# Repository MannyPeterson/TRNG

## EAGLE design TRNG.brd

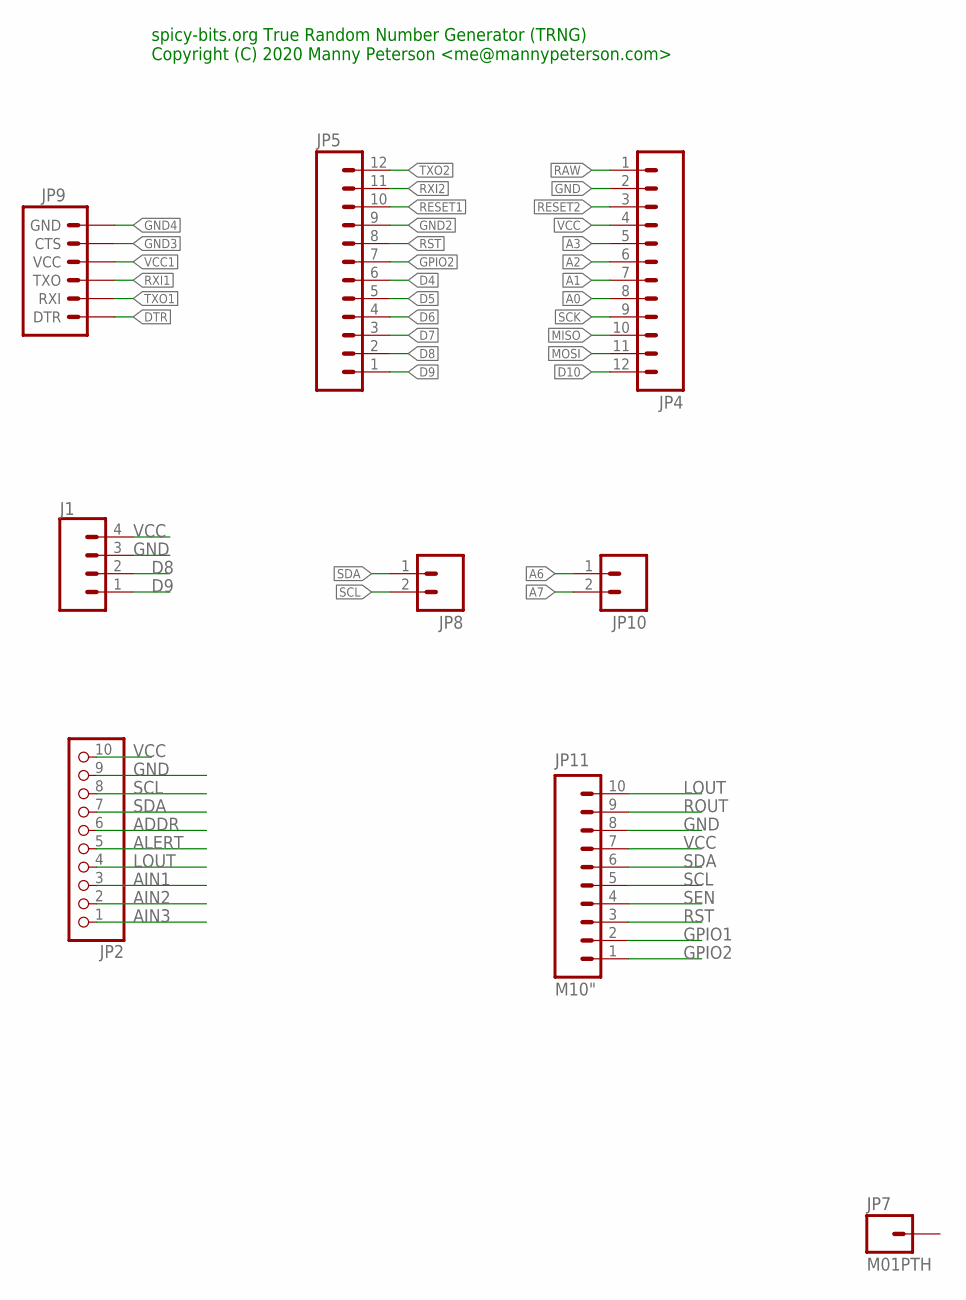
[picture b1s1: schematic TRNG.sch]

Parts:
J1: CONN_04PTH; 1X04
JP2: HEADER-1X1070MIL; 1X10_ROUND70
JP4, JP5: M12PTH; 1X12
JP7: M01PTH; 1X01
JP8, JP10: M02PTH; 1X02
JP9: ARDUINO_SERIAL_PROGRAMPTH; 1X06
JP11: M10"; 1X10

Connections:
A0: JP4.8
A1: JP4.7
A2: JP4.6
A3: JP4.5
A6: JP10.1
A7: JP10.2
ADDR: JP2.6
AIN1: JP2.3
AIN2: JP2.2
AIN3: JP2.1
ALERT: JP2.5
D4: JP5.6
D5: JP5.5
D6: JP5.4
D7: JP5.3
D8: J1.2, JP5.2
D9: J1.1, JP5.1
D10: JP4.12
DTR: JP9.1 (DTR)
GND: J1.3, JP2.9, JP4.2, JP11.8
GND2: JP5.9
GND3: JP9.5 (CTS)
GND4: JP9.6 (GND)
GPIO1: JP11.2
GPIO2: JP5.7, JP11.1
LOUT: JP2.4, JP11.10
MISO: JP4.10
MOSI: JP4.11
RAW: JP4.1
RESET1: JP5.10
RESET2: JP4.3
ROUT: JP11.9
RST: JP5.8, JP11.3
RXI1: JP9.3 (TXO)
RXI2: JP5.11
SCK: JP4.9
SCL: JP2.8, JP8.2, JP11.5
SDA: JP2.7, JP8.1, JP11.6
SEN: JP11.4
TXO1: JP9.2 (RXI)
TXO2: JP5.12
VCC: J1.4, JP2.10, JP4.4, JP11.7
VCC1: JP9.4 (VCC)

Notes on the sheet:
spicy-bits.org True Random Number Generator (TRNG) Copyright (C) 2020 Manny Peterson <me@mannypeterson.com>

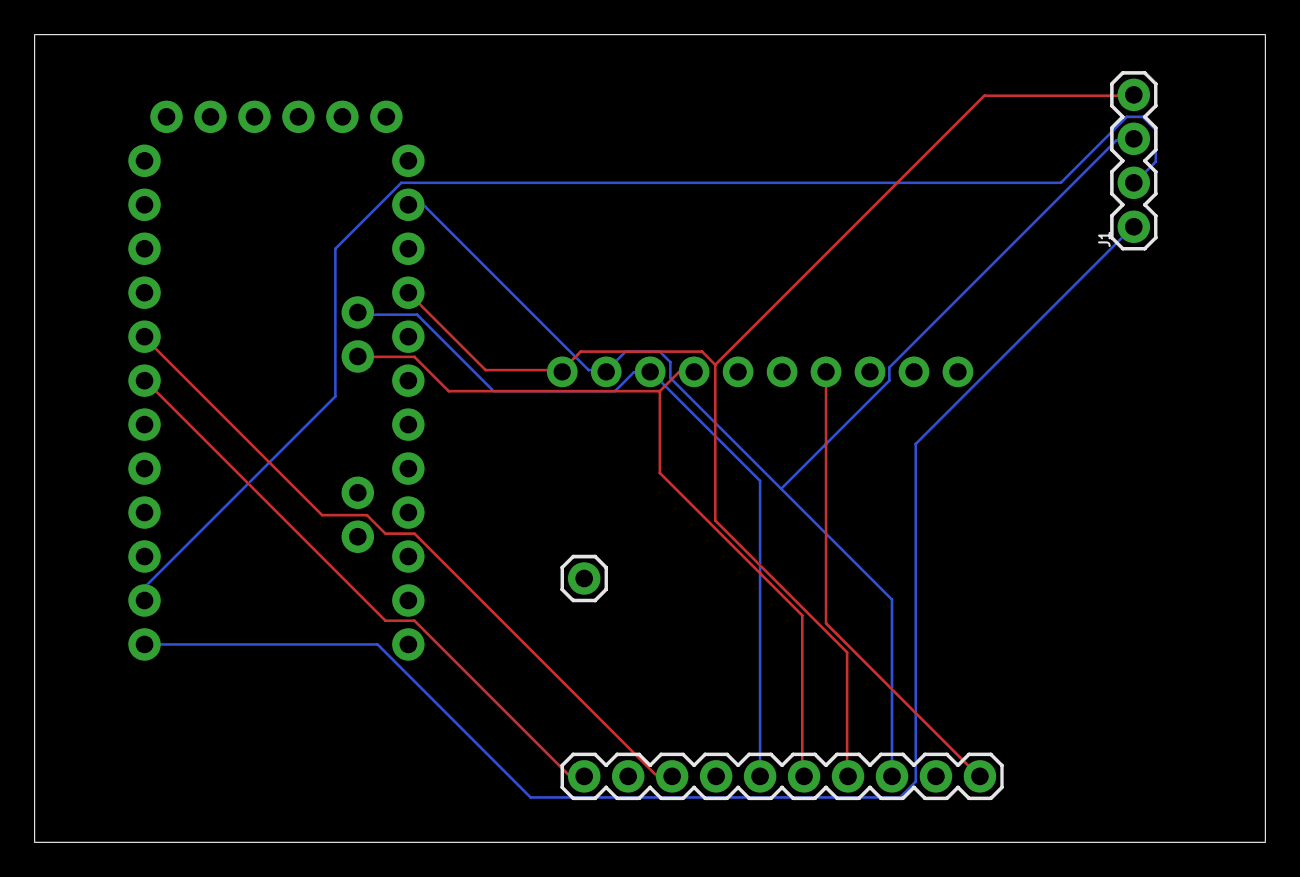
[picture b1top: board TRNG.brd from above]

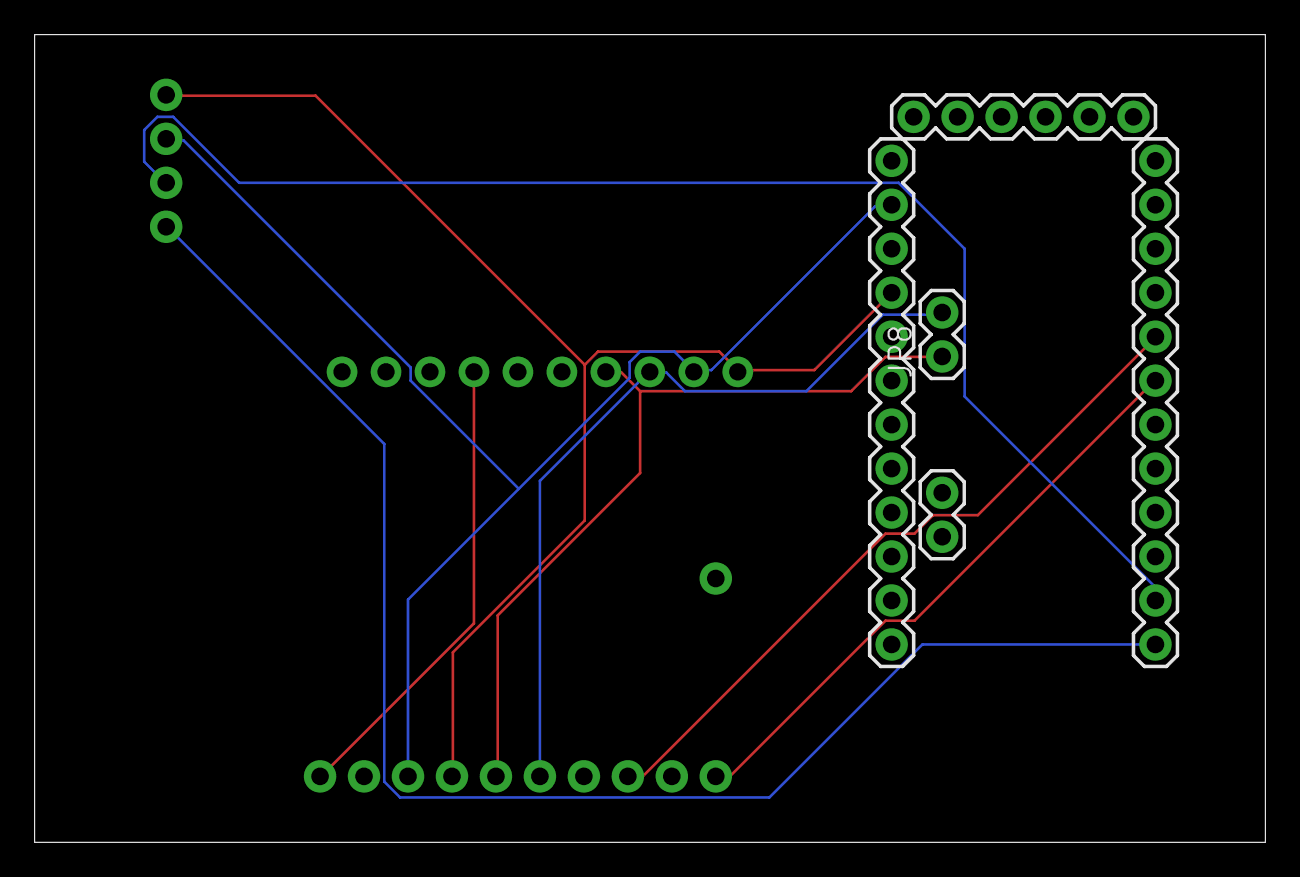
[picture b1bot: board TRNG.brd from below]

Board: 2 copper layers, 71.1 x 46.7 mm, 9 parts (5 on the bottom side), 9 nets.

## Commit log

2020-03-14 updat

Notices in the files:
parts and their libraries:
SparkFun-Connectors: Licensing: CC v3.0 Share-Alike You are welcome to use this library for commercial purposes.
